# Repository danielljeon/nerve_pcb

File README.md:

# nerve_pcb

PCB for CAN-based control systems dev platform.

- Firmware: [`nerve`](https://github.com/danielljeon/nerve).

---

<details markdown="1">
  <summary>Table of Contents</summary>

<!-- TOC -->
* [nerve_pcb](#nerve_pcb)
  * [1 Overview](#1-overview)
  * [2 Board Specifications](#2-board-specifications)
    * [2.1 Connectors](#21-connectors)
    * [2.2 Switches & Jumpers](#22-switches--jumpers)
  * [3 Release Notes](#3-release-notes)
    * [3.1 v0.1.0-alpha](#31-v010-alpha)
    * [3.2 v0.1.0-beta](#32-v010-beta)
    * [3.3 v0.1.0 (WIP)](#33-v010-wip)
  * [💖 Sponsors](#-sponsors)
    * [PCBWay](#pcbway)
      * [Why PCBWay?](#why-pcbway)
<!-- TOC -->

</details>

---

This project is sponsored by **PCBWay**. You can learn more about their valuable
support here: [💖 Sponsors/PCBWay](#pcbway).

---

## 1 Overview

|                                Top                                |                                 Bottom                                  |
|:-----------------------------------------------------------------:|:-----------------------------------------------------------------------:|
|                       |                       |
|  |  |
|        |        |

- Middle row pictures show 4 Layer assembly variant of `nerve_pcb`,
  v0.1.0-alpha.
- Bottom row pictures show `nerve_pcb`, v0.1.0-beta.

---

## 2 Board Specifications

### 2.1 Connectors

Connectors fixed by hardware (PCB traces or the connector itself).

| Connector                       | Ref | Description                                                                    |
|---------------------------------|:---:|--------------------------------------------------------------------------------|
| Tag-Connect TC2050              | J1  | Programming/debug connector                                                    |
| USB-C 5 V power                 | J2  | Power only USB-C, primary 5 V source                                           |
| BOOT0 jumper                    | J3  | Open for run flash memory (pull-down on open)                                  |
| Hinge microSD card              | J4  | Portable storage, see [Molex product video](https://youtu.be/YY2V8z6UK7M?t=95) |
| Top side 2x8 board-to-board     | J5  | See schematic/layout for details                                               |
| Bottom side 2x10 board-to-board | J6  | See schematic/layout for details                                               |
| UART3                           | J7  | Pin 1: UART3 RX, Pin 2: UART3 TX                                               |
| CAN1 (Transceiver U7)           | J8  | Pin 1: CAN1 High, Pin 2: CAN1 Low                                              |
| CAN2 (Transceiver U8)           | J9  | Pin 1: CAN2 High, Pin 2: CAN2 Low                                              |

### 2.2 Switches & Jumpers

User controllable hardware and/or firmware driven inputs.

| Switch/Jumper           | Ref | Description                                    |
|-------------------------|:---:|------------------------------------------------|
| MCU NRESET switch       | SW1 | Generic 6 mm TH button, push to reset          |
| MCU PA0 switch          | SW2 | Generic 6 mm TH button, designed for SYS_WKUP0 |
| MCU 3.3VBATT            | JP1 | Bridge to short 3.3 V supply to MCU VBAT       |
| SDIO card detect jumper | JP2 | Open = card detected, closed = not detected    |
| BNO085 clock select     | JP3 | Open = crystal, closed = external/internal     |
| BMP390 I2C address      | JP4 | Open = `0x76`, closed = `0x77`                 |

---

## 3 Release Notes

### 3.1 v0.1.0-alpha

- Pre-release 4-layer development board variant.
- `nerve_pcb_dev`, commit 76bec6f.
    - Original commit on a different repo for automated workflow reasons.
    - Closest commit on this repo
      is [f2d1f21](https://github.com/danielljeon/nerve_pcb/commit/f2d1f21cb11d7a693d17076e7c4d2955f681dbfa).
- Order date: 2024/11/15.
- Order number: `W837000ASB3`.

### 3.2 v0.1.0-beta

- Pre-release 6-layer board variant.
    - Short-term pre-release board bring-up/testing release.
- Order date: 2025/01/13.

### 3.3 v0.1.0 (WIP)

- Minor changes from the previous `v0.1.0-beta` pre-release version.
    - CAN termination design switched from single 120 ohm termination to split
      60 ohm termination with 4.7 nF capacitor.

---

## 💖 Sponsors

### PCBWay

This project is sponsored by [**PCBWay**](https://www.pcbway.com), whose PCB
manufacturing services are essential in producing high-quality prototypes for
its development. Their support ensures reliable boards that meet the project's
demands.

#### Why PCBWay?

PCBWay stands out for their exceptional services and commitment to the
community:

- **PCB Manufacturing**: High-quality fabrication with options for multilayer,
  rigid-flex, and advanced designs.
- **PCB Assembly**: Comprehensive solutions, including soldering, component
  sourcing, and assembly.
- **CNC Machining & 3D Printing**: Additional prototyping options to support
  complete product development.
- **Fast Turnaround**: Reliable and quick production times to keep projects on
  schedule.
- **Support for Open Source & Education**: PCBWay actively sponsors projects and
  provides educational resources like tutorials, videos, and documentation,
  empowering developers and hobbyists.
    - This commitment to education and open-source advocacy was a key factor in
      choosing them as a partner 🙂.

Their dedication to professional-grade services and fostering innovation makes
PCBWay an invaluable partner in bringing this project to life.

Learn more here: [Why PCBWay?](https://www.pcbway.com/why.html)

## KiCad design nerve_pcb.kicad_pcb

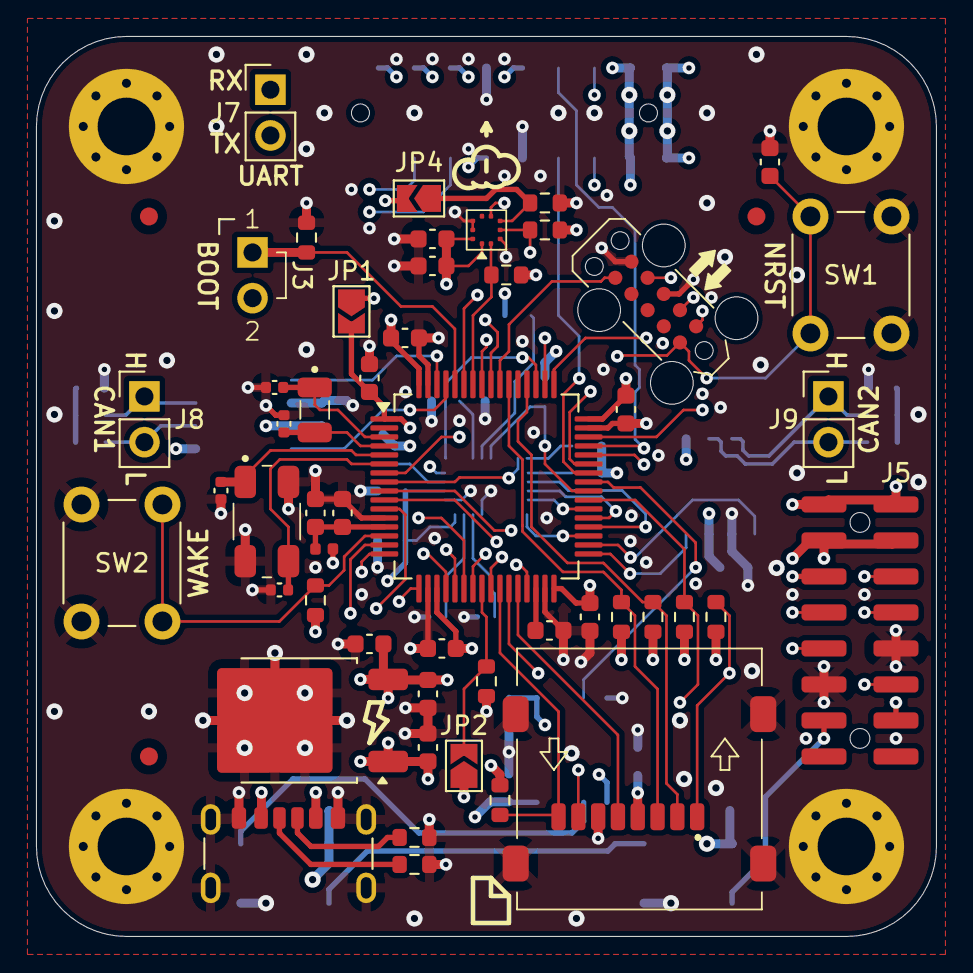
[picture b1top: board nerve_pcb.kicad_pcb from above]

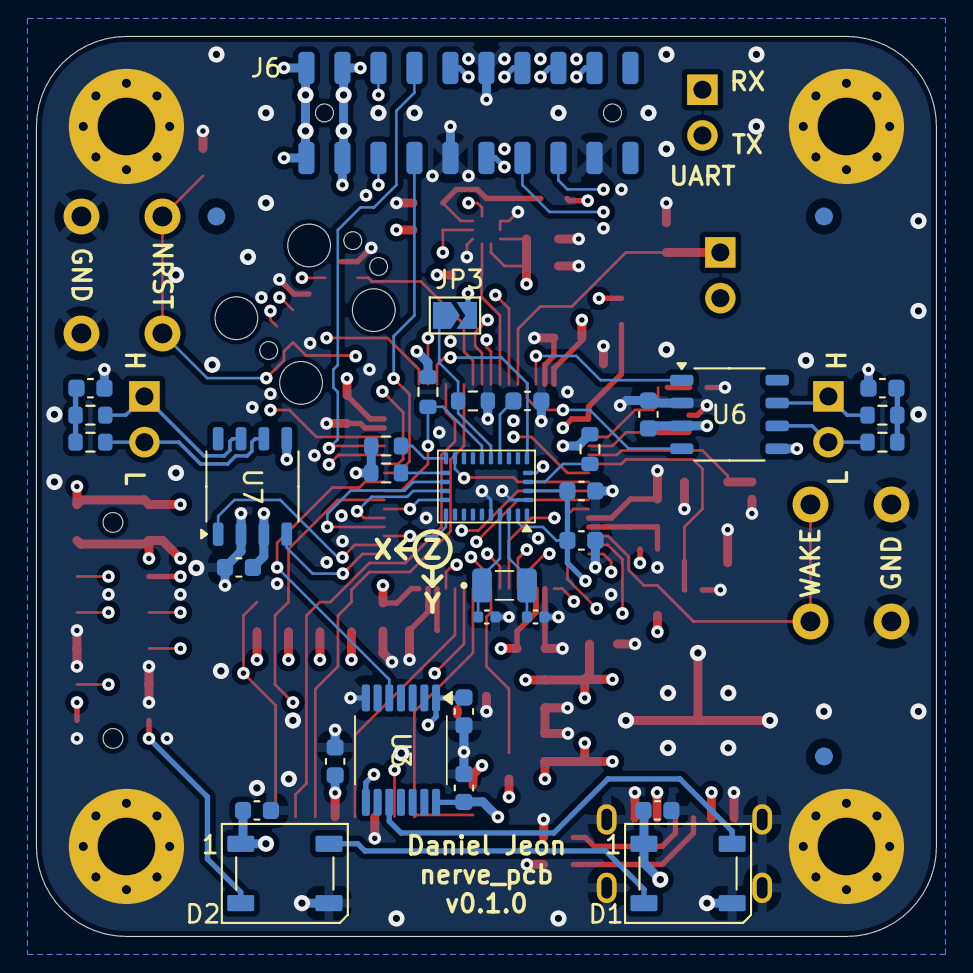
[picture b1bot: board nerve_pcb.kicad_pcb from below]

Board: 6 copper layers, 50.0 x 50.0 mm, 92 parts (35 on the bottom side), 75 nets.

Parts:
C1, C3: 1u; C_0603_1608Metric
C2: 10n; C_0603_1608Metric
C4, C17: 2u2; C_0603_1608Metric
C5, C6, C7, C8, C10, C11, C12, C15, C16, C20, C21, C22, C23, C26, C27, C28, C29, C30: 100n; C_0603_1608Metric
C9: 4u7; C_0603_1608Metric
C13, C14: 30p; C_0402_1005Metric
C18, C19, C24, C25: 18p; C_0402_1005Metric
C31, C32: 4n7; C_0603_1608Metric
D1, D2: WS2812B; LED_WS2812B_PLCC4_5.0x5.0mm_P3.2mm
FM1, FM2, FM3, FM4, FM5, FM6: 1mm; Fiducial_1mm_Mask2mm
H1, H2, H3, H4: M3; MountingHole_3.2mm_M3_Pad_Via
J1: TC2050-IDC; tag_connect_tc2050-idc
J2: 2171750001; molex_2171750001_usb_c_6p
J3: harwin_2p_2-54_jumper_open
J4: 472192001; molex_472192001_microsd_hinge
J5: BF030-16A-B1-0360-0277-0600-LB; bf030-16a-b1-0360-0277-0600-lb
J6: BF080-20-A-1-L-C; bf080-20-a-1-l-c
J7: UART; PinHeader_1x02_P2.54mm_Vertical
J8: CAN1; PinHeader_1x02_P2.54mm_Vertical
J9: CAN2; PinHeader_1x02_P2.54mm_Vertical
JP1, JP2, JP3, JP4: Open; SolderJumper-2_P1.3mm_Open_TrianglePad1.0x1.5mm
L1: 39n; L_0402_1005Metric
R1, R2: 5k1; R_0603_1608Metric
R3, R9, R10, R11, R12, R13, R16, R17, R18: 10k; R_0603_1608Metric
R4, R5, R6, R7, R8: 47k; R_0603_1608Metric
R14, R15: 2k2; R_0603_1608Metric
R19, R20, R21, R22: 60R; R_0603_1608Metric
SW1, SW2: SPST; SW_PUSH_6mm
U1: ld39150dt33-r; to-252-2_dpak-2-leg
U2: STM32F446RET; LQFP-64_10x10mm_P0.5mm
U3: TXB0104QPWRQ1; txb0104qpwrq1
U4: BNO085; bno085
U5: BMP390; bmp390
U6, U7: TJA1051T/3; sot96-1_soic-8
Y1: 8M; ecs_ecx-64
Y2, Y3: 32k768; ecs_ecx-34r

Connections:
+3.3VA: C1.1, C2.1, L1.2, U2.13 (VDDA)
+3.3VBATT: C10.1, J5.13, JP1.2 (B), U2.1 (VBAT)
+3V3: C4.1, C5.1, C6.1, C7.1, C8.1, C9.1, C12.1, C15.1, C22.1, C23.1, C27.1, C28.1, J1.1 (VCC), J3.2, J4.4 (VDD), J5.3, J5.4, J6.3, J6.4, JP1.1 (A), JP2.1 (A), JP3.2 (B), JP4.2 (B), L1.1, R3.1, R4.1, R5.1, R6.1, R7.1, R8.1, R11.1, R12.1, R14.1, R15.1, R16.1, R17.1, U1.3 (VO), U2.19 (VDD), U2.32 (VDD), U2.48 (VDD), U2.64 (VDD), U3.1 (V_{CCA}), U3.8 (OE), U4.3 (V_{DD}), U4.5 (PS1), U4.28 (V_{DDIO}), U5.1 (V_{DDIO}), U5.6 (CSB), U5.10 (V_{DD}), U6.5 (V_{IO}), U7.5 (V_{IO})
+5V: C3.1, C16.1, C20.1, C21.1, C29.1, C30.1, D1.1 (VDD), D2.1 (VDD), J2.A9 (VBUS), J2.B9 (VBUS), J5.1, J5.2, J6.1, J6.2, U1.1 (VI), U3.14 (V_{CCB}), U6.3 (V_{CC}), U7.3 (V_{CC})
/BOOT0: J3.1, R9.1, U2.60 (BOOT0)
/CAN1_RX: U2.61 (PB8), U6.4 (RXD)
/CAN1_TX: U2.62 (PB9), U6.1 (TXD)
/CAN2_RX: U2.33 (PB12), U7.4 (RXD)
/CAN2_TX: U2.34 (PB13), U7.1 (TXD)
/EXTI0_IMU_INT: U2.8 (PC0), U4.14 (H_INTN)
/GPIO_GPS_RST: J5.11, U2.15 (PA1)
/GPIO_IMU_P0: U2.51 (PC10), U4.6 (PS0/WAKE)
/GPIO_IMU_RST: R12.2, U2.40 (PC9), U4.11 (NRST)
/GPIO_RADIO_RST: J6.9, U2.50 (PA15)
/GPIO_SPI2_CS: U2.37 (PC6), U4.18 (H_CSN)
/HSE_IN: C13.1, U2.5 (PH0_OSC_HSE_IN), Y1.1
/HSE_OUT: C14.1, U2.6 (PH1_OSC_HSE_OUT), Y1.3
/I2C1_SCL: R17.2, U2.58 (PB6), U5.2 (SCK)
/I2C1_SDA: R16.2, U2.59 (PB7), U5.4 (SDI)
/LSE_IN: C18.1, U2.3 (PC14_OSC32_LSE_IN), Y2.1
/LSE_OUT: C19.1, U2.4 (PC15_OSC32_LSE_OUT), Y2.2
/NRST: C11.2, J1.10 (~RESET), SW1.2, U2.7 (NRST)
/PA4: J6.17, U2.20 (PA4)
/PA5: J6.15, U2.21 (PA5)
/PA6: J6.14, U2.22 (PA6)
/PA7: J6.16, U2.23 (PA7)
/PB4: J6.13, U2.56 (PB4)
/PB5: J6.12, U2.57 (PB5)
/PC1: J5.6, U2.9 (PC1)
/PC2: J5.8, U2.10 (PC2)
/PC3: J5.10, U2.11 (PC3)
/SDIO_CLK: J4.5 (CLK), U2.28 (PB2)
/SDIO_CMD: J4.3 (CMD), R6.2, U2.54 (PD2)
/SDIO_D0: J4.7 (DAT0), R5.2, U2.39 (PC8)
/SDIO_D1: J4.8 (DAT1), R4.2, U2.26 (PB0)
/SDIO_D2: J4.1 (DAT2), R8.2, U2.27 (PB1)
/SDIO_D3: J4.2 (DAT3/CD), R7.2, U2.52 (PC11)
/SDIO_DET: JP2.2 (B), R10.1, U2.24 (PC4)
/SPI2_MISO: U2.35 (PB14), U4.20 (H_SDA/H_MISO/TX)
/SPI2_MOSI: U2.36 (PB15), U4.17 (SA0/H_MOSI)
/SPI2_SCK: U2.38 (PC7), U4.19 (H_SCL/SCK/RX)
/SWCLK: J1.4 (SWCLK/TCK), U2.49 (PA14)
/SWDIO: J1.2 (SWDIO/TMS), U2.46 (PA13)
/SWO: J1.6 (SWO/TDO), U2.55 (PB3)
/TIM1_CH1_PWM: U2.41 (PA8), U3.5 (A4)
/TIM1_CH1_PWM_{5V}: D1.4 (DIN), U3.10 (B4)
/USART1_CTS: J6.5, U2.44 (PA11)
/USART1_RTS: J6.7, U2.45 (PA12)
/USART1_RX: J6.6, U2.43 (PA10)
/USART1_TX: J6.8, U2.42 (PA9)
/USART2_RX: J5.5, U2.17 (PA3)
/USART2_TX: J5.7, U2.16 (PA2)
/USART3_RX: J7.1, U2.25 (PC5)
/USART3_TX: J7.2, U2.29 (PB10)
/WS2812B_PWM: D2.2 (DOUT), J5.14
/nerve_pcb_can/CAN1+: J8.1, R20.1, U6.7 (CANH)
/nerve_pcb_can/CAN1-: J8.2, R19.1, U6.6 (CANL)
/nerve_pcb_can/CAN2+: J9.1, R22.1, U7.7 (CANH)
/nerve_pcb_can/CAN2-: J9.2, R21.1, U7.6 (CANL)
GND: C1.2, C2.2, C3.2, C4.2, C5.2, C6.2, C7.2, C8.2, C9.2, C10.2, C11.1, C12.2, C13.2, C14.2, C15.2, C16.2, C17.2, C18.2, C19.2, C20.2, C21.2, C22.2, C23.2, C24.2, C25.2, C26.2, C27.2, C28.2, C29.2, C30.2, C31.2, C32.2, D1.3 (VSS), D2.3 (VSS), H1.1, H2.1, H3.1, H4.1, J1.3 (GND), J1.5 (GND/VPROG), J2.A12 (GND), J2.B12 (GND), J2.S1 (SHIELD), J4.6 (VSS), J4.G1 (GND), J4.G2 (GND), J4.G3 (GND), J4.G4 (GND), J5.9, J5.12, J6.10, J6.11, J6.18, R1.2, R2.2, R9.2, R10.2, R13.2, R18.2, SW1.1, SW2.2, U1.2 (GND), U2.12 (VSSA), U2.18 (VSS), U2.31 (VSS), U2.47 (VSS), U2.63 (VSS), U3.7 (GND), U4.2 (GND), U4.25 (GND), U5.3 (V_{SS}), U5.8 (V_{SS}), U5.9 (V_{SS}), U6.2 (GND), U7.2 (GND), Y1.2, Y1.4
unnamed: C31.1, R19.2, R20.2
unnamed: C32.1, R21.2, R22.2
unnamed: D1.2 (DOUT), D2.4 (DIN)
unnamed: J2.A5 (CC1), R2.1
unnamed: J2.B5 (CC2), R1.1
unnamed: JP3.1 (A), R13.1, U4.10 (CLKSEL0)
unnamed: JP4.1 (A), R18.1, U5.5 (SDO)
unnamed: R3.2, SW2.1, U2.14 (PA0)
unnamed: C17.1, U2.30 (VCAP_1)
unnamed: R11.2, U4.4 (BOOTN)
unnamed: C26.1, U4.9 (CAP)
unnamed: R14.2, U4.15 (ENV_SCL)
unnamed: R15.2, U4.16 (ENV_SDA)
unnamed: C25.1, U4.27 (XIN32), Y3.2
unnamed: C24.1, U4.26 (XOUT32/CLKSEL1), Y3.1

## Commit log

2024-11-15 Add gitignore and CODEOWNERS
2024-11-15 Add component_library submodule
2024-11-15 Add KiBot workflow
2024-11-15 Update component_library submodule
2024-11-15 Update component_library (again)
2024-11-15 Update component_library (again x2)
2024-11-15 Add initial schematics
2024-11-16 Update schematics
2024-11-16 Update board settings
2024-11-16 Initial main PCB layout (no traces)
2024-11-16 Clean up pre-route layout
2024-11-16 Add schematic changes from PCB routing/layout
2024-11-16 Add mounting holes to secondary schematics
2024-11-16 Add WIP PCB
2024-11-16 Update schematics for add-on PCB separation
2024-11-16 Update refs on schematics
2024-11-16 Add breakout connectors to add-on PCBs
2024-11-16 Clean up schematics and add footprints
2024-11-16 Add stackup note on main schematic
2024-11-17 Revert to 603 package sizes and add WIP PCB
2024-11-17 Swap to 1.27mm board-to-board and WIP PCB
2024-11-17 Split and remove add-on board designs
2024-11-17 Add missing power flag
2024-11-17 Fix board-to-board connector pinout
2024-11-17 Move PCB dimensions to User Comments layer
2024-11-17 Swap to 6-layer stackup
2024-11-17 Move 2x8 board-to-board connector
2024-11-18 Pass DRC (ERC previously passed)
2024-11-18 Add KiBot badge in README.md
2024-11-19 Combine KiBot BoM directory
2024-11-19 Clean up schematics and ensure PCB parity
2024-11-19 Adjust BMP390 address jumper and cleanup PCB
2024-11-19 Add impedance control settings and PCB notes
2024-11-19 Add differential pair CAN lines
2024-11-19 Fix impedance control PCB notes
2024-11-19 Update KiBot PCB PDF gen
2024-11-19 Fix bad config.kibot.yaml
2024-11-20 Add ground stitching vias and silkscreen cleanup
2024-11-20 Add layer docs and settings
2024-11-20 Nuke silkscreen and cleanup fab layers
2024-11-21 Cleanup PCB
2024-11-21 Add CAN 120ohm resistors
2024-11-21 Resolve broken links from previous commit
2024-11-21 Add silkscreen drawings
2024-11-22 Fix silkscreen overlapping via
2024-11-22 Add Vbatt unused jumper
2024-11-22 Update component_library
2024-11-23 Cleanup Vbatt circuit and fix silkscreen
2024-11-25 Adjust design for easy swap to 4 layer stackup
2024-12-03 Add docs PCB pictures
2024-12-03 Add markdown TOC
2024-12-03 Cleanup schematic and propagate changes
2024-12-03 Update KiBot workflow
2024-12-06 Schematic corrections
    - Add decoupling caps for sensor ICs
    - Fix clock circuits
    - Add BNO085 clock jumper
    - Minor cleanup
2024-12-07 Major stackup revision
2024-12-08 Major stackup revision and cleanup
2024-12-08 Update docs pictures
2024-12-08 Fix HSE clock caps
2024-12-08 Simplify clock circuits
2024-12-08 Update IMU clock circuit and cleanup
2024-12-08 Swap 32k768 crystal caps to 18pF
2024-12-09 Add MIT license
2024-12-09 Update README.md and include sponsors
2024-12-09 Add README.md pictures
2024-12-09 Add release notes
2024-12-11 Add new symbol and footprint libraries
2024-12-11 Update J5 2x8 GPS connector
2024-12-11 Cleanup and update 2x10 Radio connector
2024-12-12 Cleanup schematic and change J7 footprint
2024-12-12 Add WS2812Bs
2024-12-12 Fix D2 position for symmetry
2024-12-12 Fix via position to prevent USB-C short
2024-12-13 Cleanup and add fiducials
2024-12-14 Add design notes on schematic
2024-12-14 Fix BNO085 circuit for SPI
2024-12-15 Switch UART breakout to vertical pins
2024-12-16 Cleanup schematics and PCB
2024-12-16 Fix minor via inconsistency
2024-12-17 Major routing cleanup
2024-12-17 Add missing IMU silkscreen graphic
2024-12-24 Fix DRC and rename pages in prep for v0.1.0-beta
2024-12-25 Update component_library and cleanup unused pads
2024-12-27 Fix schematic notes
2025-01-03 Update component library and tables
2025-01-03 Fix mounting hole thermal reliefs
2025-01-04 Readd net colours
2025-01-05 Fix bad via position
2025-01-07 Fix BNO085 circuit and touchups
2025-01-09 Major cleanup and add missing transfer vias
2025-01-13 Cleanup silkscreen
2025-01-14 Update docs for release
2025-01-22 Switch to split CAN termination
2025-01-23 Update IMU silkscreen graphic
2025-02-19 Fix minor Markdown syntax
2025-02-19 Update Markdown sponsor writing for clarity
2025-02-19 Improve Markdown HTML image alt text
2025-04-03 Update for KiCad 9.0 and component library
2025-04-03 Update KiBot workflow for v2_k9
2025-04-03 Update footprint and symbol library
2025-04-26 Add minor decoupling caps
2025-04-26 Update component library and pictures
2025-04-26 Fix silkscreen over via
2025-04-26 Attempt fix KiBot workflow warning step
2025-04-30 add imagen render
2025-05-05 Add WS2812B decoupling caps and PCB cleanup
2025-05-14 Update README.md for PCB-firmware references
2025-05-27 Cleanup and fix outer layer non-functional pads
2025-06-03 Update config.kibot.yaml for KiCad/Bot 9
2025-10-18 Fix and update pictures
